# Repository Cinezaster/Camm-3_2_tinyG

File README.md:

# Camm-3_2_tinyG
Converting a Roland Camm-3 PNC-3000 CNC to a TinyG controller

## Spindle controller
An arduino reading the speed and adjust the phase of the power to the motor to hold target speed
* speed read
* spindle on/off read 
* target speed read
* pid control on motor

## Screen
Shows the status of the CNC {x,y,z,spindle speed, feedrate}

## Kill switch
A box with a big red kill switch, connected to reset.

## Auto height
Connect Z-min to GND.

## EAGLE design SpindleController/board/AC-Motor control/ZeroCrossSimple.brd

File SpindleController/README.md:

#AC-Motor Speedcontroller

## Features
* Read ON/OFF signal from CNC Controller
* Read PWM out from CNC Controller
* Measures speed of the spindle
* Using PID control to set and hold speed
* Zero crossing detection to set phase control on AC line to motor

## Board

* H11AA1S AC opto coupler to detect the zero point crossing
* SDV2415R random triggered Solid State Relay
* R1 & R2 22K Ohm 2Watt resistors

## Arduino Leonardo pins
* Zero Crossing input --> Pin 3 (interrupt 0)
* Speed puls input --> Pin 2 (interrupt 1)
* Duty cycle read input --> Pin 7 (interrupt 4)
* Spindle ON/OFF input --> Pin 6
* (RX CNC board --> Pin 1 (TX))
* (TX CNC board --> Pin 0 (RX))
* Phase puls output --> Pin 5
* Oled MOSI --> Pin SPI MOSI (Pin 14)
* Oled CLK --> Pin SPI CLK (Pin 15)
* Oled Reset --> Pin 8
* Oled Dc --> Pin 9
* Oled CS --> Pin 10

## Flow idea1
1. init everything that is needed
2. check Spindle ON/OFF input
3. if Spindle ON/OFF goes HIGH wait 200 Millis and read duty of pwm onspeed puls input
4. Start zero crossing detection and measure speed
5. Calculate PID control
6. Trigger AC Phase pulse output
7. print speed to screen over spi
8. go back to 4 and repeat until Spindle ON/OFF goes LOW

## Zero Crossing detection
Peak at 3V has a measured width of 400 micro seconds

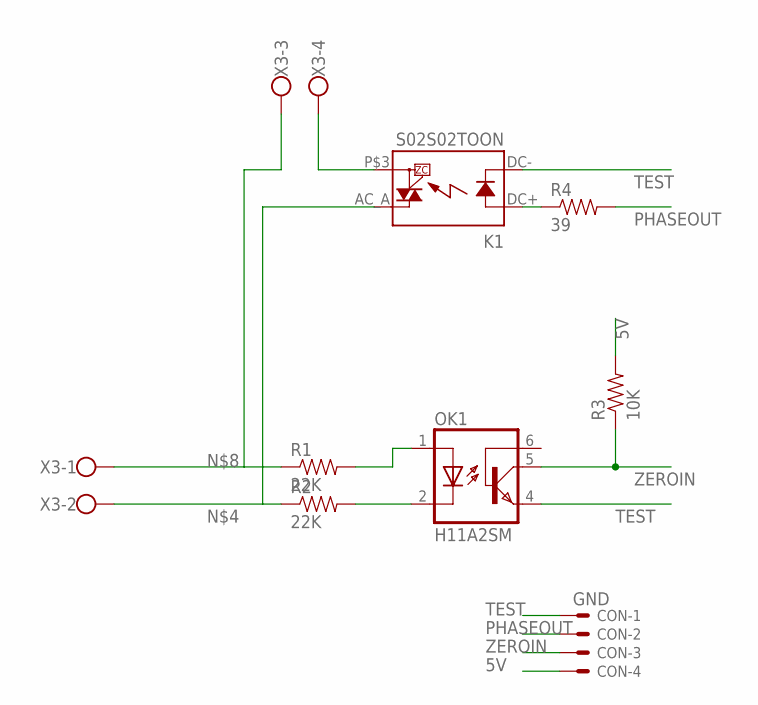
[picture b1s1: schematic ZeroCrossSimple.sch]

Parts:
CON: GND; KK-156-4
K1: S02S02TOON; TOON
OK1: H11A2SM; DIL6-SMD
R1, R2: 22K; R2512
R3: 10K; 0805
R4: 39; 0805
X3: W237-4

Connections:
5V: CON.4, R3.2
unnamed: OK1.1 (A), R1.2
unnamed: OK1.2 (C), R2.2
unnamed: K1.P$3 (DS2), X3.4
unnamed: K1.AC_A (DS1), R2.1, X3.2
unnamed: K1.DC+ (A), R4.1
unnamed: R1.1, X3.1, X3.3
PHASEOUT: CON.2, R4.2
TEST: CON.1, K1.DC- (K), OK1.4 (EMI)
ZEROIN: CON.3, OK1.5 (COL), R3.1

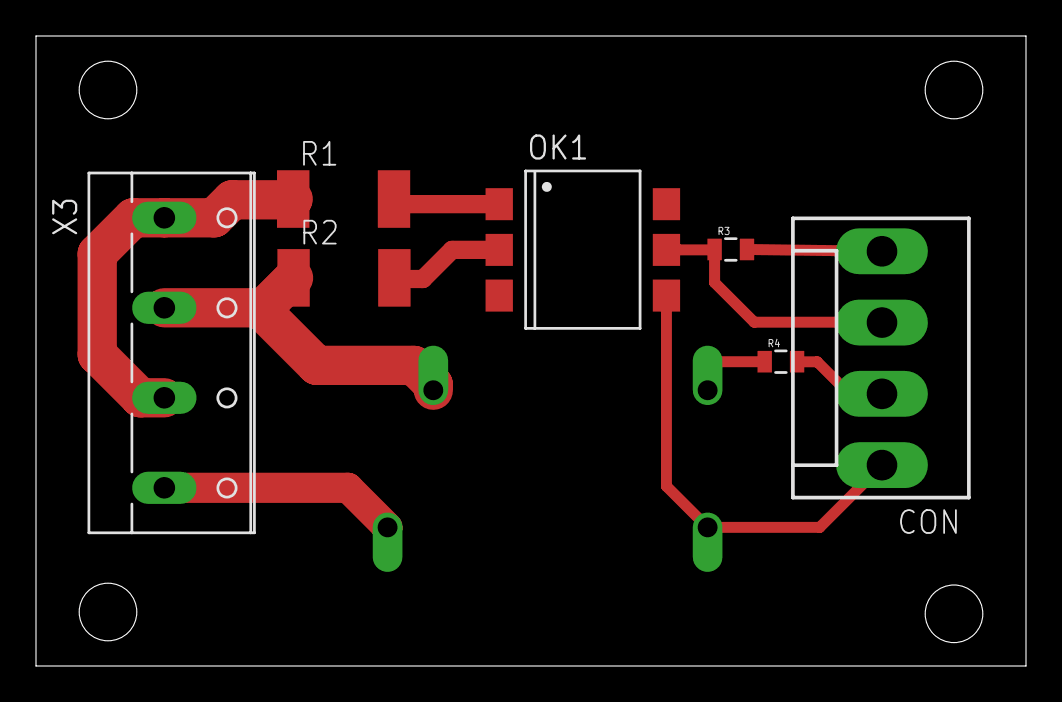
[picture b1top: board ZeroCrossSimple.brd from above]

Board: 2 copper layers, 55.0 x 35.0 mm, 8 parts (1 on the bottom side), 10 nets.

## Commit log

2015-01-17 project explaination
2015-01-17 first init of speedCount
2015-01-27 Create gh-pages branch via GitHub
2015-01-27 initial settings
2015-01-27 spindle controller add read
2015-01-27 change?
2015-01-27 Beter code wrapping
2015-02-13 added board
2015-02-13 update link to picture
2015-02-18 x y reversed direction
2015-02-18 update on arduino pinout
2015-02-19 merge
2015-02-21 spindle controller first shot
2015-03-16 add lcd screen + documentation
2015-03-26 Testing hardware and interrupt flow
2015-03-26 fix merge
2015-05-19 no pid controller

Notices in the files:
parts and their libraries:
SparkFun-Passives: Licensing: Creative Commons ShareAlike 4.0 International - https://creativecommons.org/licenses/by-sa/4.0
